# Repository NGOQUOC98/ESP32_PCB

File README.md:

# BMS-HW

## Hardware

### Schematics

### PCB Layout

#### Top side

#### Bot side

### Solder Mask

#### Top side

### Dimension

### 3D

#### Top side

#### Back side

### Gerber

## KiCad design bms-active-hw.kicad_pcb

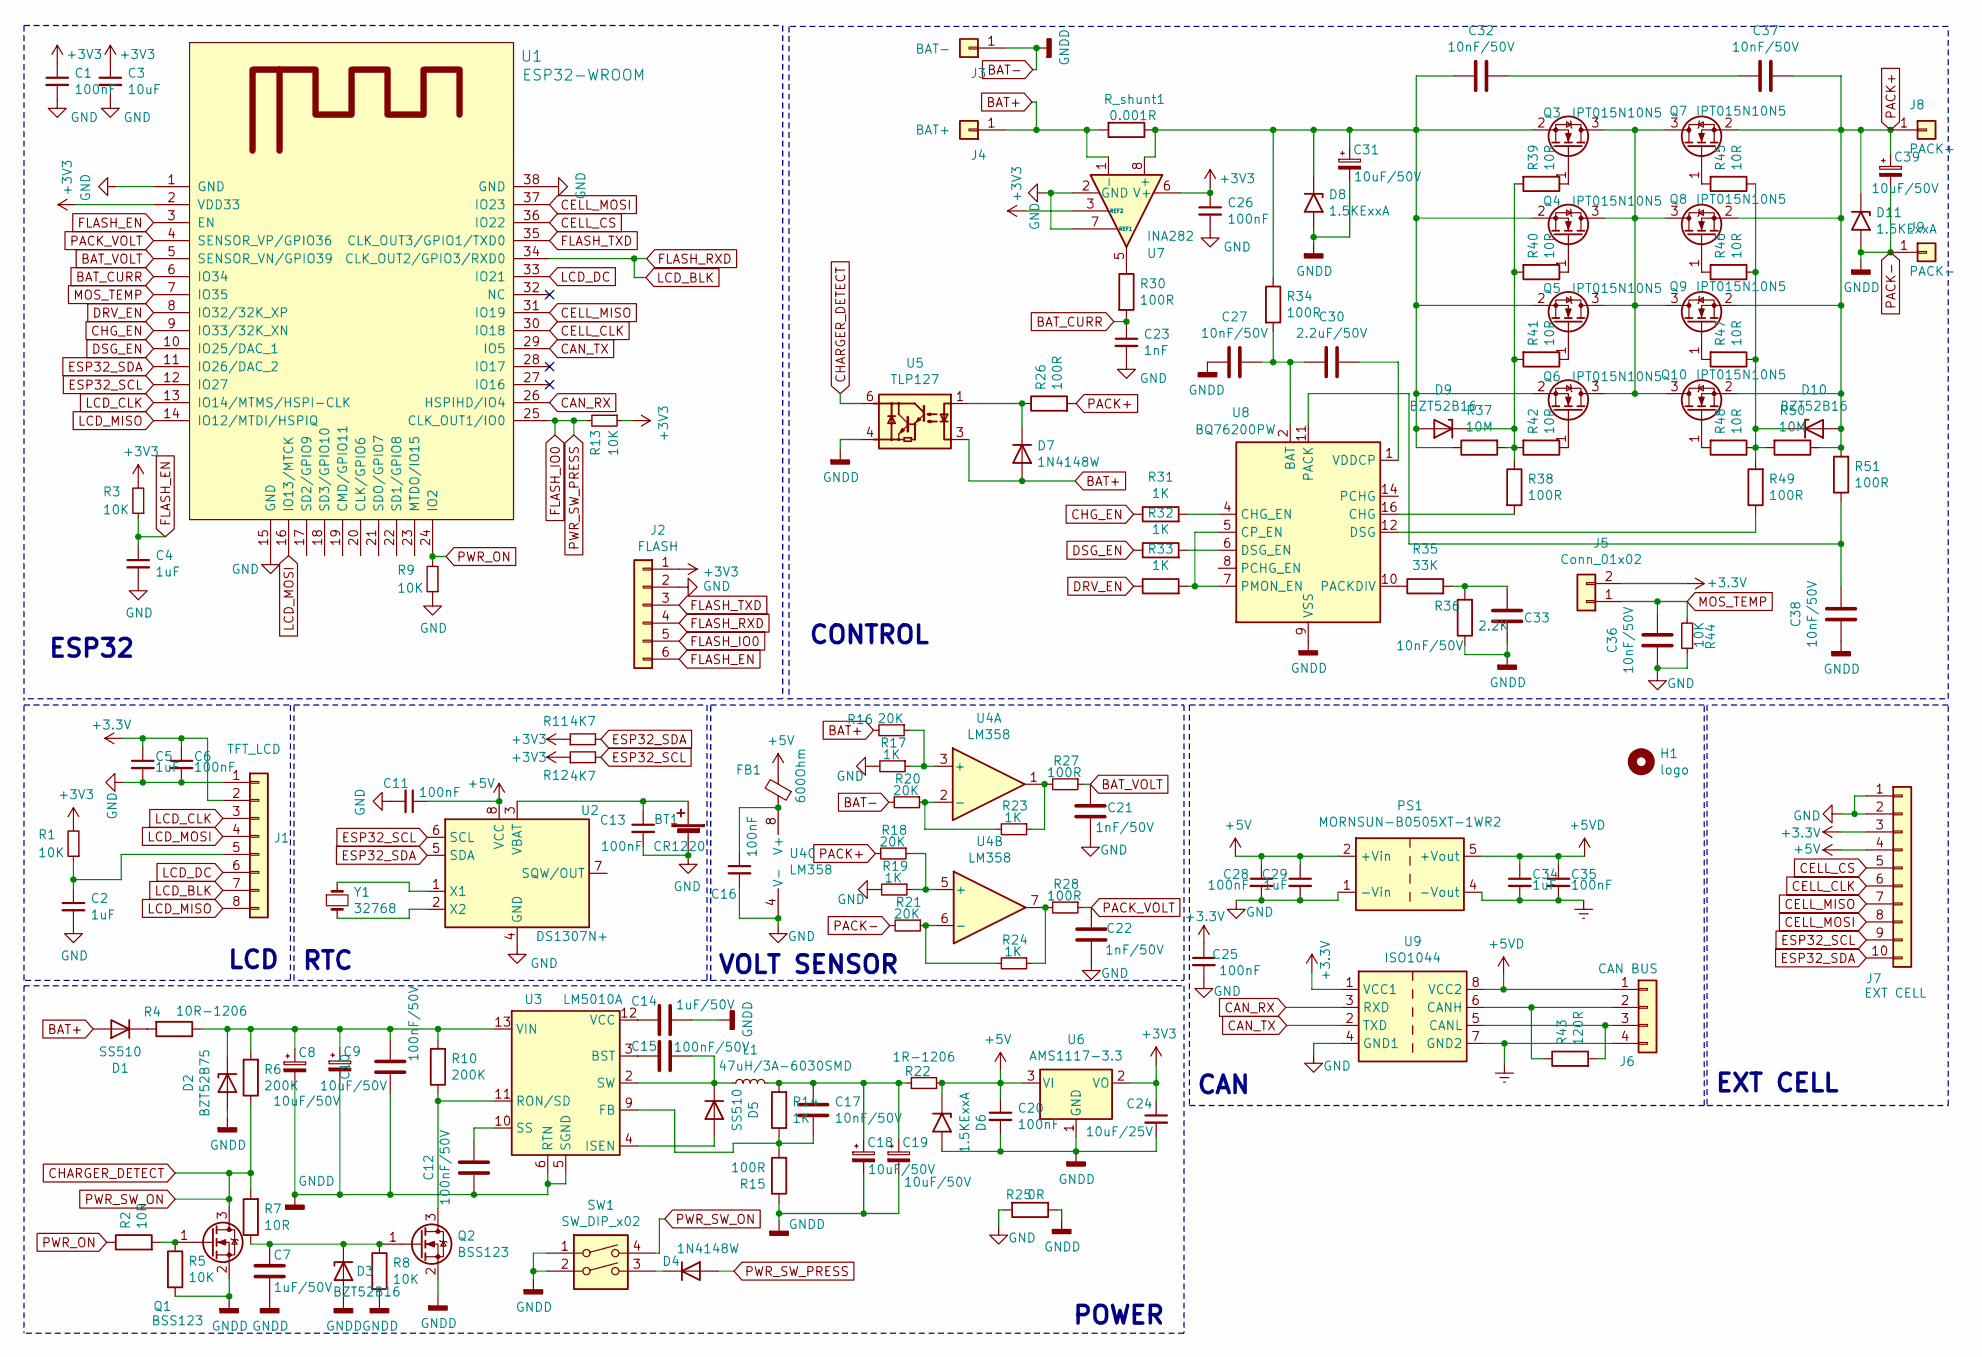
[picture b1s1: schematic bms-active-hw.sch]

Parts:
BT1: CR1220; BAT_CR1220_Holder
C1, C11, C13, C20, C26: 100nF; C_0603_1608Metric
C2, C4: 1uF; C_0603_1608Metric
C3: 10uF; C_1210_3225Metric
C5, C29, C34: 1uF; C_0805_2012Metric
C6, C16, C25, C28, C35: 100nF; C_0805_2012Metric
C7, C14: 1uF/50V; C_0805_2012Metric
C8, C9, C18, C19, C31, C39: 10uF/50V; C_1210_3225Metric
C10, C12, C15: 100nF/50V; C_0805_2012Metric
C17, C27, C32, C33, C36, C37, C38: 10nF/50V; C_0805_2012Metric
C21, C22: 1nF/50V; C_0805_2012Metric
C23: 1nF; C_0603_1608Metric
C24: 10uF/25V; C_1206_3216Metric
C30: 2.2uF/50V; C_0805_2012Metric
D1, D5: SS510; D_SMA
D2: BZT52B75; D_SOD-123
D3, D9, D10: BZT52B16; D_SOD-123
D4, D7: 1N4148W; D_SOD-123
D6, D8, D11: 1.5KExxA; D_DO-201AE_P15.24mm_Horizontal
FB1: 600Ohm; L_0805_2012Metric
H1: logo; logo-flametech-v1
J1: TFT_LCD; TFT_DISLAY
J2: FLASH; PinHeader_1x06_P2.54mm_Vertical
J3: BAT-; PACK
J4: BAT+; PACK
J5: Conn_01x02; PinHeader_1x02_P2.54mm_Vertical
J6: CAN BUS; PinHeader_1x04_P2.54mm_Vertical
J7: EXT CELL; PinHeader_1x10_P2.54mm_Vertical
J8: PACK+; PACK
J9: PACK-; PACK
L1: 47uH/3A-6030SMD; L_Bourns_SRR1210A
PS1: MORNSUN-B0505XT-1WR2; Converter_DCDC_B0505
Q1, Q2: BSS123; SOT-23
Q3, Q4, Q5, Q6, Q7, Q8, Q9, Q10: IPT015N10N5; Infineon_PG-HSOF-8-1
R1, R3, R9, R13: 10K; R_0603_1608Metric
R2, R7, R39, R40, R41, R42, R45, R46, R47, R48: 10R; R_0805_2012Metric
R4: 10R-1206; R_0805_2012Metric
R5, R8, R44: 10K; R_0805_2012Metric
R6, R10: 200K; R_0805_2012Metric
R11, R12: 4K7; R_0603_1608Metric
R14: 1K; R_0603_1608Metric
R15, R26, R27, R28, R30, R34, R38, R49, R51: 100R; R_0805_2012Metric
R16, R18, R20, R21: 20K; R_0805_2012Metric
R17, R19, R23, R24, R31, R32, R33: 1K; R_0805_2012Metric
R22: 1R-1206; R_1206_3216Metric
R25: 0R; R_0805_2012Metric
R35: 33K; R_0805_2012Metric
R36: 2.2K; R_0805_2012Metric
R37, R50: 10M; R_0805_2012Metric
R43: 120R; R_0805_2012Metric
R_shunt1: 0.001R; R0.001ohm
SW1: SW_DIP_x02; SW_PUSH_6mm_H5mm
U1: ESP32-WROOM; ESP32-WROVER-WROOM32
U2: DS1307N+; SOIC-8_3.9x4.9mm_P1.27mm
U3: LM5010A; HTSSOP-14-1EP_4.4x5mm_P0.65mm_EP3.4x5mm_Mask3x3.1mm
U4: LM358; LM358M
U5: TLP127; MFSOP6-4_4.4x3.6mm_P1.27mm
U6: AMS1117-3.3; SOT-223-3_TabPin2
U7: INA282; INA282AID
U8: BQ76200PW; TSSOP-16_4.4x5mm_P0.65mm
U9: ISO1044; SOIC-8_3.9x4.9mm_P1.27mm
Y1: 32768; Crystal_SMD_3215-2Pin_3.2x1.5mm

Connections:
+5V: C11.1, C20.1, C28.1, C29.1, D6.1 (A1), FB1.2, J7.4, PS1.2 (+Vin), R22.2, U2.8 (VCC), U6.3 (VI)
+5VD: C34.1, C35.1, J6.1, PS1.5 (+Vout), U9.8 (VCC2)
BAT+: D1.2 (A), D7.2 (A), J4.1, R16.2, R_shunt1.2, U5.3, U7.1 (-)
BAT-: C7.1, C8.2, C9.2, C10.1, C12.1, C14.2, C18.2, C19.2, C20.2, C24.2, C27.2, C31.2, C33.1, C38.1, C39.2, D2.2 (A), D3.2 (A), D6.2 (A2), D8.2 (A2), D11.2 (A2), J3.1, J9.1, Q1.2 (S), Q2.2 (S), R5.2, R8.2, R15.1, R20.2, R21.2, R25.1, R36.1, SW1.1, SW1.2, U3.5 (SGND), U3.6 (RTN), U5.4, U6.1 (GND), U8.9 (VSS)
BAT_CURR: C23.1, R30.2, U1.6 (IO34)
BAT_VOLT: C21.2, R27.1, U1.5 (SENSOR_VN/GPIO39)
CAN_RX: U1.26 (HSPIHD/IO4), U9.3 (RXD)
CAN_TX: U1.29 (IO5), U9.2 (TXD)
CELL_CLK: J7.6, U1.30 (IO18)
CELL_CS: J7.5, U1.36 (IO22)
CELL_MISO: J7.7, U1.31 (IO19)
CELL_MOSI: J7.8, U1.37 (IO23)
CHARGER_DETECT: Q1.3 (D), R6.1, R7.2, SW1.4, U5.6
CHG_EN: R31.1, U1.9 (IO33/32K_XN)
DRV_EN: R33.1, U1.8 (IO32/32K_XP)
DSG_EN: R32.1, U1.10 (IO25/DAC_1)
ESP32_SCL: J7.9, R12.2, U1.12 (IO27), U2.6 (SCL)
ESP32_SDA: J7.10, R11.2, U1.11 (IO26/DAC_2), U2.5 (SDA)
Earth: C34.2, C35.2, J6.4, PS1.4 (-Vout), U9.7 (GND2)
FLASH_EN: C4.1, J2.6, R3.1, U1.3 (EN)
FLASH_IO0: D4.2 (A), J2.5, R13.2, U1.25 (CLK_OUT1/IO0)
FLASH_RXD: J1.7, J2.4, U1.34 (CLK_OUT2/GPIO3/RXD0)
FLASH_TXD: J2.3, U1.35 (CLK_OUT3/GPIO1/TXD0)
GND: BT1.2 (-), C1.2, C2.2, C3.2, C4.2, C5.2, C6.2, C11.2, C13.2, C16.2, C21.1, C22.1, C23.2, C25.2, C26.2, C28.2, C29.2, C36.1, J1.1, J2.2, J7.1, J7.2, PS1.1 (-Vin), R9.1, R17.2, R19.2, R25.2, R44.1, U1.1 (GND), U1.15 (GND), U1.38 (GND), U2.4 (GND), U4.4 (V-), U7.2 (GND), U7.7 (REF1), U9.4 (GND1)
LCD_CLK: J1.3, U1.13 (IO14/MTMS/HSPI-CLK)
LCD_DC: J1.6, U1.33 (IO21)
LCD_MISO: J1.8, U1.14 (IO12/MTDI/HSPIQ)
LCD_MOSI: J1.4, U1.16 (IO13/MTCK)
MOS_TEMP: C36.2, J5.1, R44.2, U1.7 (IO35)
unnamed: BT1.1 (+), C13.1, U2.3 (VBAT)
unnamed: C2.1, J1.5, R1.1
unnamed: C7.2, D3.1 (K), Q2.1 (G), R7.1, R8.1
unnamed: C8.1, C9.1, C10.2, D2.1 (K), R4.1, R6.2, R10.2, U3.13 (VIN)
unnamed: C12.2, U3.10 (SS)
unnamed: C14.1, U3.12 (VCC)
unnamed: C15.1, U3.3 (BST)
unnamed: C15.2, D5.1 (K), L1.1, U3.2 (SW)
unnamed: C16.1, FB1.1, U4.8 (V+)
unnamed: C17.1, C18.1, C19.1, L1.2, R14.2, R22.1
unnamed: C17.2, R14.1, R15.2, U3.9 (FB)
unnamed: C27.1, C30.1, R34.2, U8.2 (BAT)
unnamed: C30.2, U8.1 (VDDCP)
unnamed: C31.1, C32.1, D8.1 (A1), D9.2 (A), Q3.2 (S), Q4.2 (S), Q5.2 (S), Q6.2 (S), R34.1, R37.1, R_shunt1.1, U7.8 (+)
unnamed: C32.2, C37.1
unnamed: C33.2, R35.2, R36.2
unnamed: C38.2, R51.1, U8.11 (PACK)
unnamed: D1.1 (K), R4.2
unnamed: D4.1 (K), SW1.3
unnamed: D5.2 (A), U3.4 (ISEN)
unnamed: D7.1 (K), R26.1, U5.1
unnamed: D9.1 (K), R37.2, R38.1, R39.2, R40.2, R41.2, R42.2
unnamed: D10.1 (K), R45.1, R46.1, R47.1, R48.1, R49.2, R50.2
unnamed: J6.2, R43.1, U9.6 (CANH)
unnamed: J6.3, R43.2, U9.5 (CANL)
unnamed: Q1.1 (G), R2.2, R5.1
unnamed: Q2.3 (D), R10.1, U3.11 (RON/SD)
unnamed: Q3.1 (G), R39.1
unnamed: Q4.1 (G), R40.1
unnamed: Q5.1 (G), R41.1
unnamed: Q6.1 (G), R42.1
unnamed: Q7.1 (G), R45.2
unnamed: Q8.1 (G), R46.2
unnamed: Q9.1 (G), R47.2
unnamed: Q10.1 (G), R48.2
unnamed: Q3.3 (D), Q4.3 (D), Q5.3 (D), Q6.3 (D), Q7.3 (D), Q8.3 (D), Q9.3 (D), Q10.3 (D)
unnamed: R16.1, R17.1, U4.3 (+)
unnamed: R18.1, R19.1, U4.5 (+)
unnamed: R20.1, R23.2, U4.2 (-)
unnamed: R21.1, R24.2, U4.6 (-)
unnamed: R23.1, R27.2, U4.1
unnamed: R24.1, R28.2, U4.7
unnamed: R30.1, U7.5
unnamed: R31.2, U8.4 (CHG_EN)
unnamed: R32.2, U8.6 (DSG_EN)
unnamed: R33.2, U8.5 (CP_EN), U8.7 (PMON_EN)
unnamed: R35.1, U8.10 (PACKDIV)
unnamed: R38.2, U8.16 (CHG)
unnamed: R49.1, U8.12 (DSG)
unnamed: U2.1 (X1), Y1.1
unnamed: U2.2 (X2), Y1.2
PACK+: C37.2, C39.1, D10.2 (A), D11.1 (A1), J8.1, Q7.2 (S), Q8.2 (S), Q9.2 (S), Q10.2 (S), R18.2, R26.2, R50.1, R51.2
PACK_VOLT: C22.2, R28.1, U1.4 (SENSOR_VP/GPIO36)
PWR_ON: R2.1, R9.2, U1.24 (IO2)

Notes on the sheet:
ESP32
RTC
LCD
POWER
VOLT SENSOR
CAN
EXT CELL
CONTROL

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
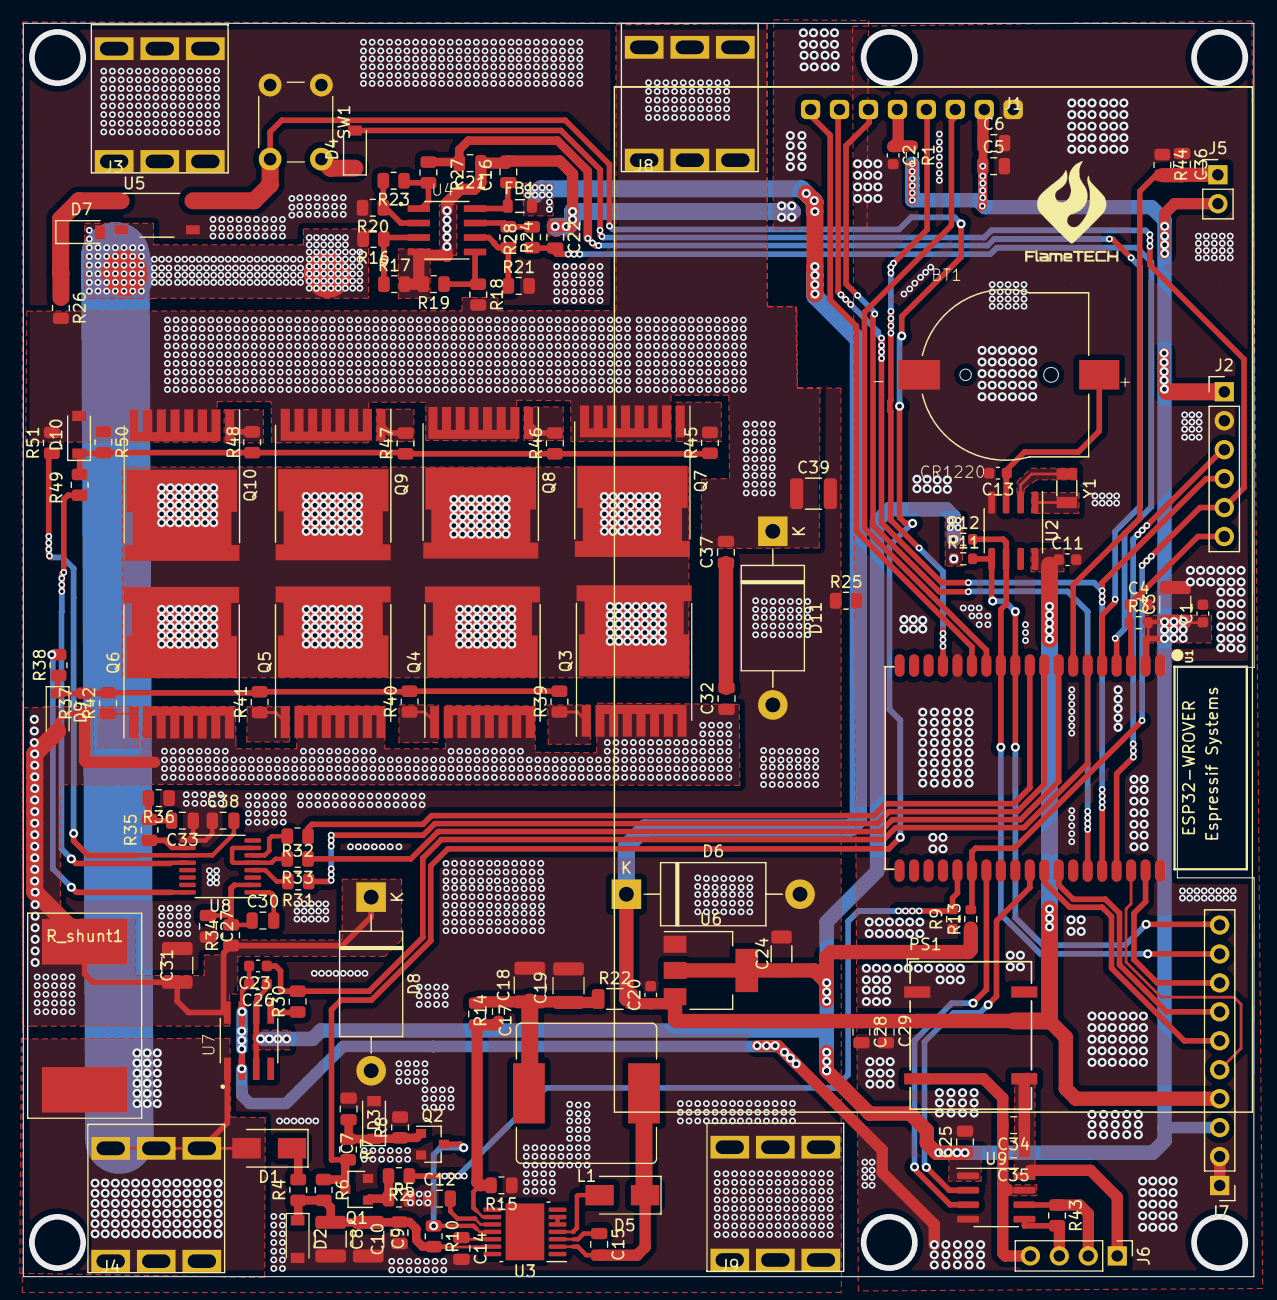
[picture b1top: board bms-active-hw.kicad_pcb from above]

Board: 2 copper layers, 108.0 x 110.0 mm, 136 parts (0 on the bottom side), 84 nets.

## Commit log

2021-01-09 add file
